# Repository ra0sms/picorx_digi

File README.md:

# SDR receiver Pico RX for DIGI modes

This is a clone of Jon Dawson's project [PicoRX SDR](https://github.com/dawsonjon/PicoRX).

But I wanted to make a simple DIGI (WSPR, FT8) receiver. This modification works with PC and WSJT-X software by one USB Type-C cable. 3.5 mm audio output is just for sound control. Audio from receiver to PC goes through USB connection.

More information - https://ra0sms.com/picorx-digi-modes

Firmware for 3 type of boards - https://github.com/ra0sms/picorx_digi/tree/main/firmware

Gerber files - https://github.com/ra0sms/picorx_digi/blob/main/KiCad/pico_rx/gerber_picorxdigi.zip

More pictures - https://github.com/ra0sms/picorx_digi/tree/main/pics

Schematic - https://github.com/ra0sms/picorx_digi/blob/main/KiCad/pico_rx/pipicorx.pdf

## Settings

You need to connect receiver to PC by USB cable. And select COM-port and Audio input like on the pictures below.

Or if you use FLrig software

Now you can see decodes.

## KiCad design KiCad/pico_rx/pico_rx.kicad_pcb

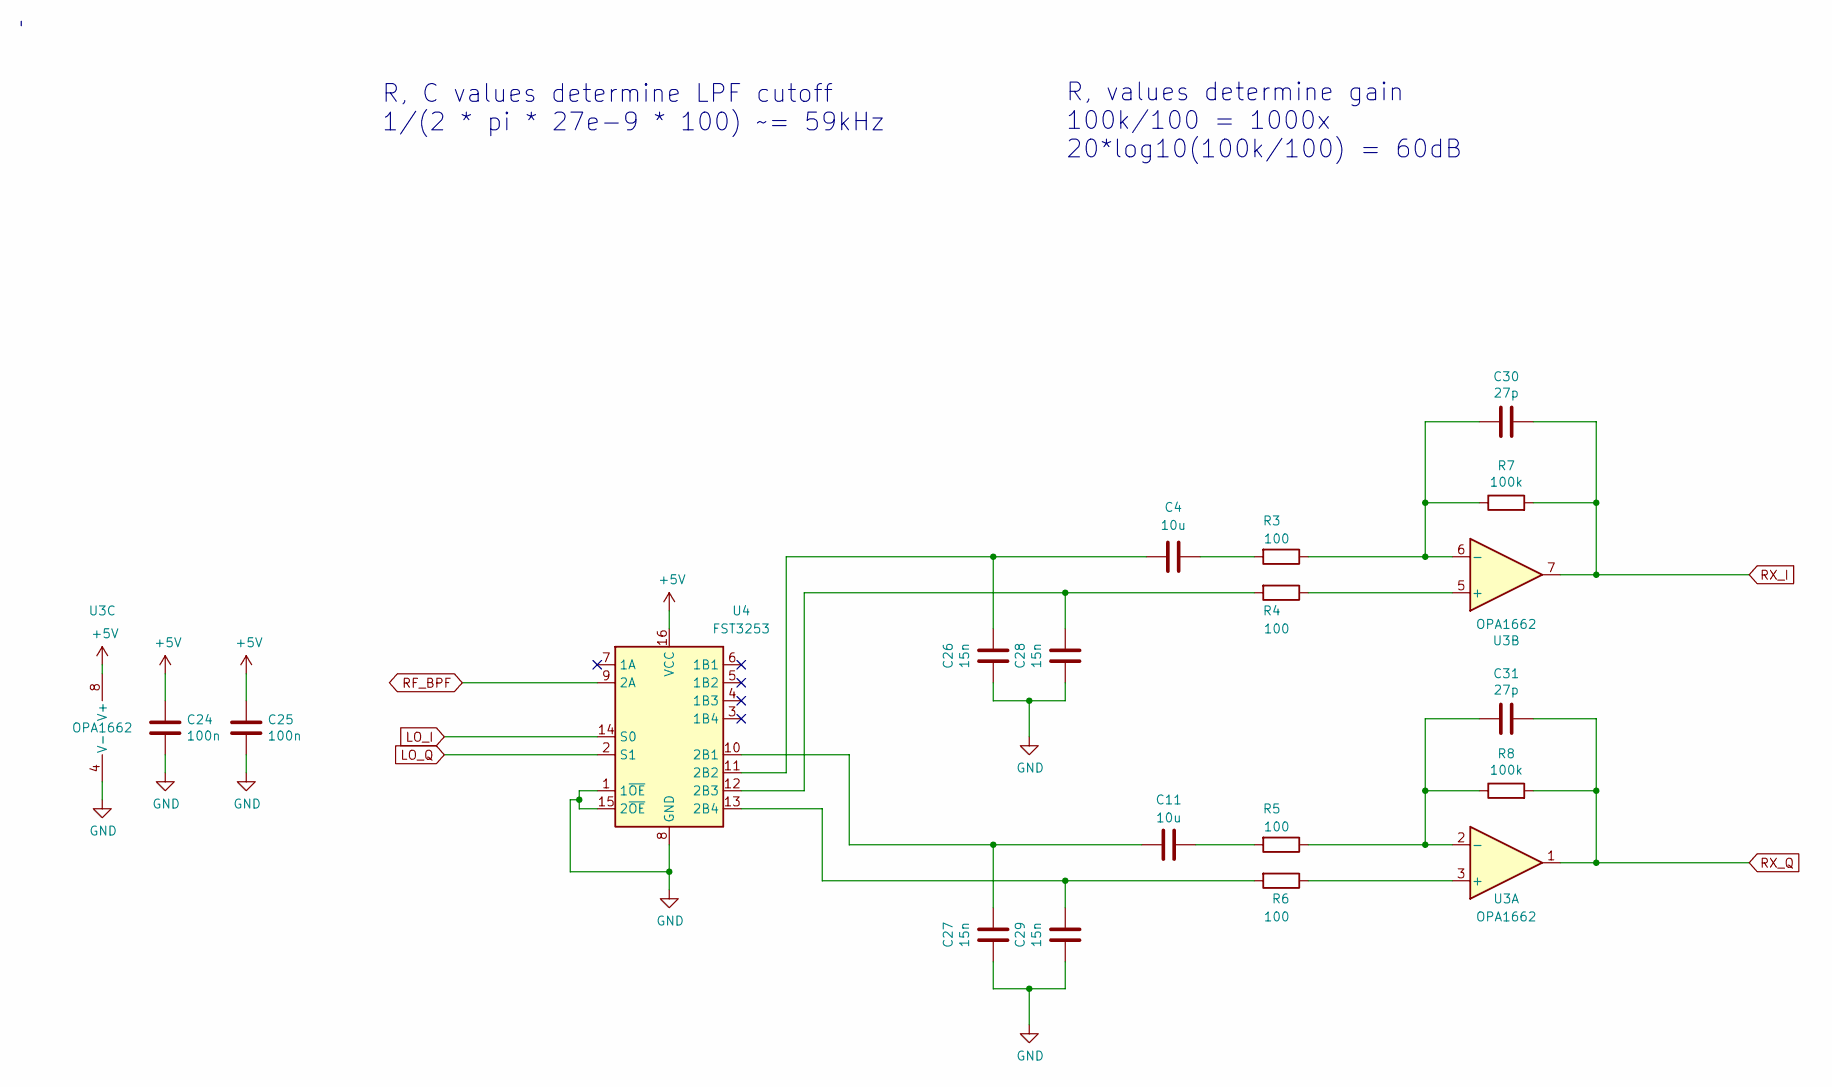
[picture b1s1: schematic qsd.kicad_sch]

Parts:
C4, C11: 10u; C_1206_3216Metric
C24, C25: 100n; C_1206_3216Metric
C26, C27, C28, C29: 15n; C_1206_3216Metric
C30, C31: 27p; C_1206_3216Metric
R3, R4, R5, R6: 100; R_1206_3216Metric
R7, R8: 100k; R_1206_3216Metric
U3: OPA1662; SO-8_3.9x4.9mm_P1.27mm
U4: FST3253; SOIC-16_3.9x9.9mm_P1.27mm

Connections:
+5V: C24.1, C25.1, U3.8 (V+), U4.16 (VCC); also elsewhere on the board
GND: C24.2, C25.2, C26.1, C27.1, C28.1, C29.1, U3.4 (V-), U4.1 (1~OE), U4.8 (GND), U4.15 (2~OE); also elsewhere on the board
LO_I: U4.14 (S0); also elsewhere on the board
LO_Q: U4.2 (S1); also elsewhere on the board
unnamed: C4.1, R3.2
unnamed: C11.1, R5.2
unnamed: R6.1, U3.3 (+)
unnamed: C31.1, R5.1, R8.1, U3.2 (-)
unnamed: R4.1, U3.5 (+)
unnamed: C30.1, R3.1, R7.1, U3.6 (-)
unnamed: C11.2, C27.2, U4.10 (2B1)
unnamed: C4.2, C26.2, U4.11 (2B2)
unnamed: C28.2, R4.2, U4.12 (2B3)
unnamed: C29.2, R6.2, U4.13 (2B4)
RF_BPF: U4.9 (2A); also elsewhere on the board
RX_I: C30.2, R7.2, U3.7; also elsewhere on the board
RX_Q: C31.2, R8.2, U3.1; also elsewhere on the board

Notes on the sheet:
R, values determine gain 100k/100 = 1000x 20*log10(100k/100) = 60dB
R, C values determine LPF cutoff 1/(2 * pi * 27e-9 * 100) ~= 59kHz

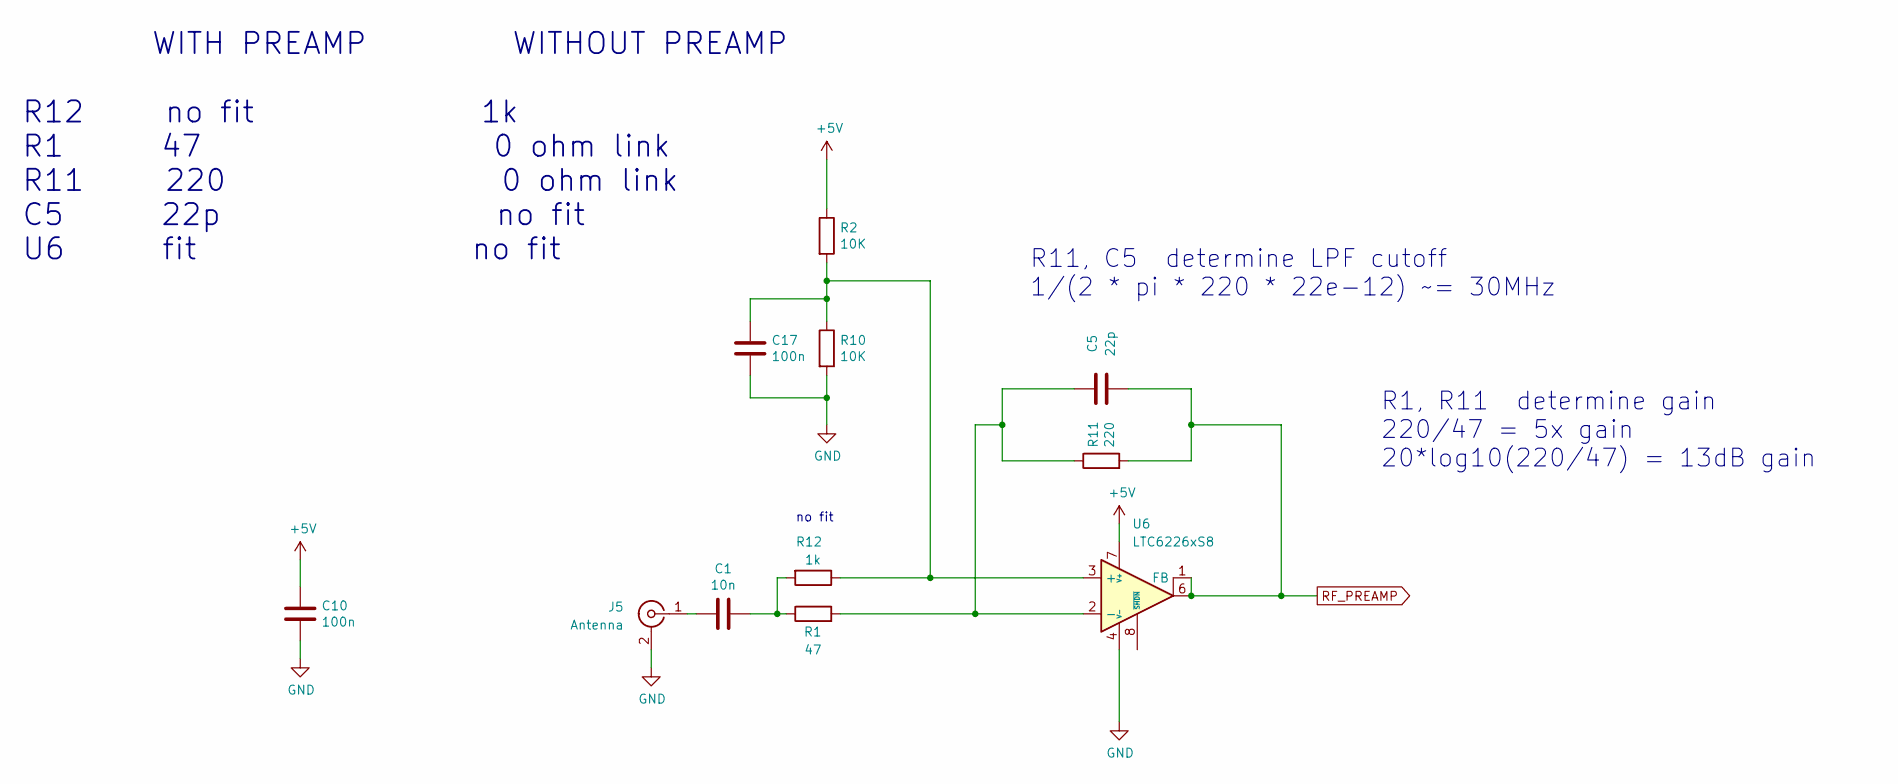
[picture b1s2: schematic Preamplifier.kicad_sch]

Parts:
C1: 10n; C_1206_3216Metric
C5: 22p; C_1206_3216Metric
C10, C17: 100n; C_1206_3216Metric
J5: Antenna; SMA_BAT_Wireless_BWSMA-KWE-Z001
R1: 47; R_1206_3216Metric
R2, R10: 10K; R_1206_3216Metric
R11: 220; R_1206_3216Metric
R12: 1k; R_1206_3216Metric
U6: LTC6226xS8; SO-8_3.9x4.9mm_P1.27mm

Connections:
+5V: C10.1, R2.1, U6.7 (V+); also elsewhere on the board
GND: C10.2, C17.2, J5.2 (Ext), R10.2, U6.4 (V-), U6.5 (V-); also elsewhere on the board
unnamed: C1.1, R1.1, R12.2
unnamed: C1.2, J5.1 (In)
unnamed: C17.1, R2.2, R10.1, R12.1, U6.3 (+)
unnamed: C5.1, R1.2, R11.1, U6.2 (-)
RF_PREAMP: C5.2, R11.2, U6.1 (FB), U6.6; also elsewhere on the board

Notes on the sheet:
no fit
R11, C5 determine LPF cutoff 1/(2 * pi * 220 * 22e-12) ~= 30MHz
WITH PREAMP WITHOUT PREAMP R12 no fit 1k R1 47 0 ohm link R11 220 0 ohm link C5 22p no fit U6 fit no fit
R1, R11 determine gain 220/47 = 5x gain 20*log10(220/47) = 13dB gain

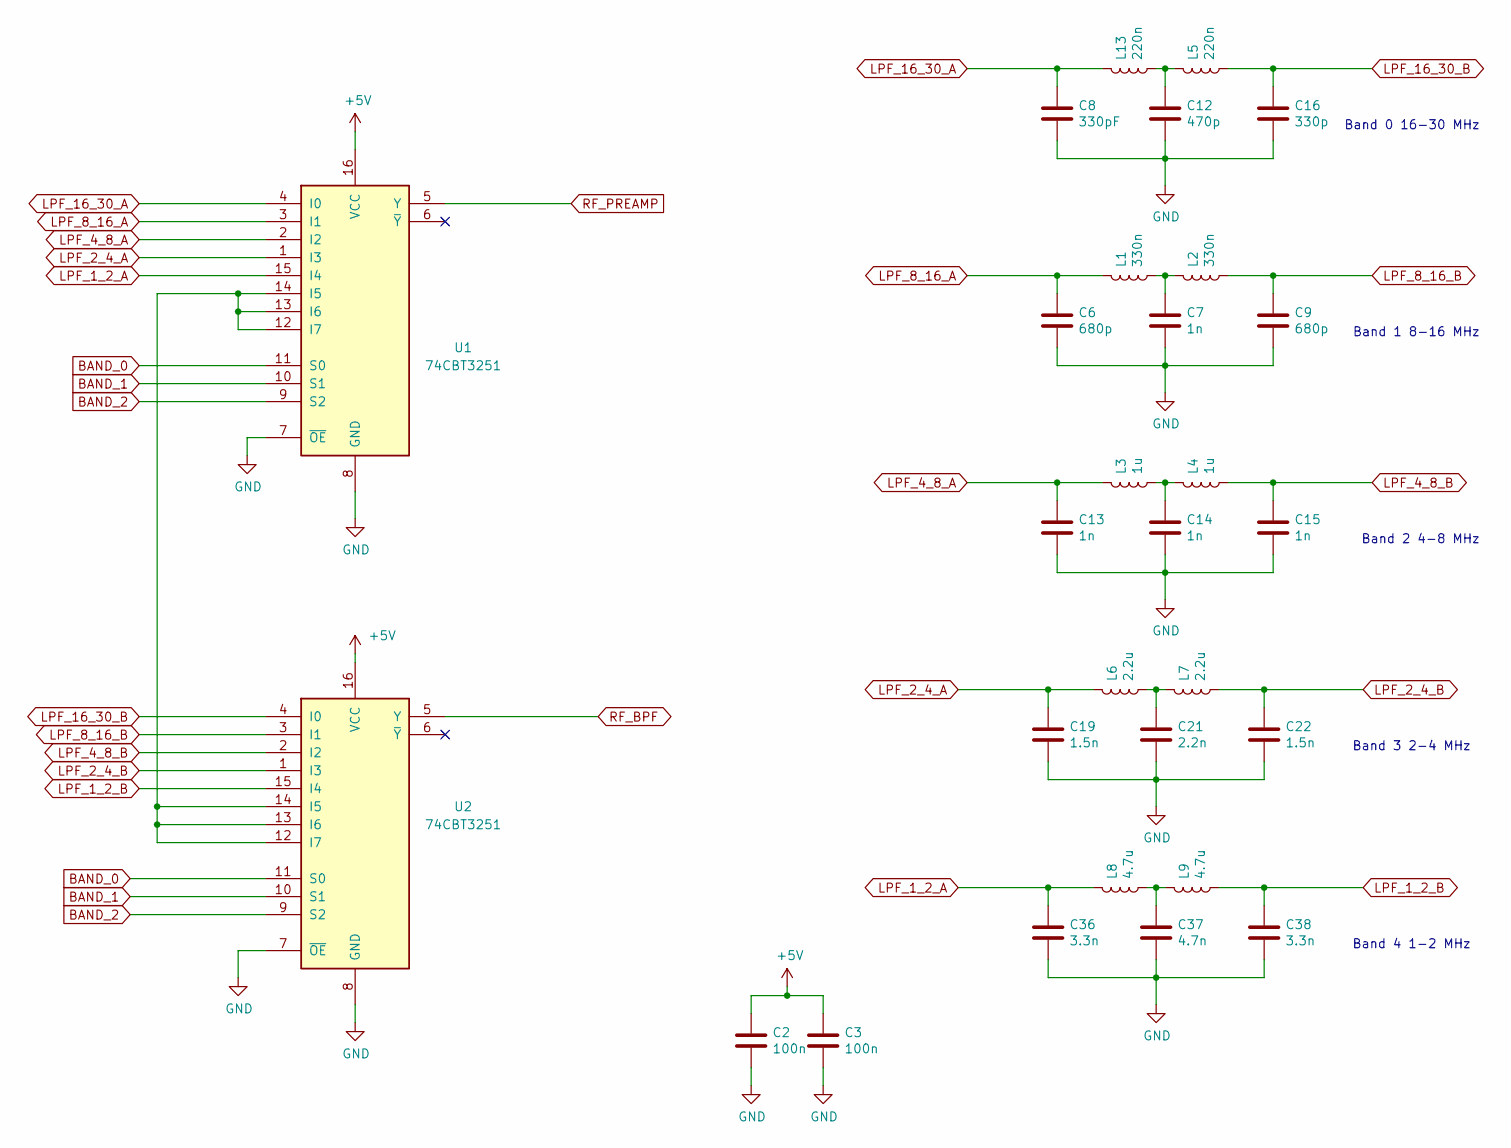
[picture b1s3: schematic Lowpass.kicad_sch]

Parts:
C2, C3: 100n; C_1206_3216Metric
C6, C9: 680p; C_0805_2012Metric
C7, C13, C14, C15: 1n; C_0805_2012Metric
C8: 330pF; C_0805_2012Metric
C12: 470p; C_0805_2012Metric
C16: 330p; C_0805_2012Metric
C19, C22: 1.5n; C_0805_2012Metric
C21: 2.2n; C_0805_2012Metric
C36, C38: 3.3n; C_0805_2012Metric
C37: 4.7n; C_0805_2012Metric
L1, L2: 330n; L_0805_2012Metric_Pad1.05x1.20mm_HandSolder
L3, L4: 1u; L_0805_2012Metric_Pad1.05x1.20mm_HandSolder
L5, L13: 220n; L_0805_2012Metric_Pad1.05x1.20mm_HandSolder
L6, L7: 2.2u; L_0805_2012Metric_Pad1.05x1.20mm_HandSolder
L8, L9: 4.7u; L_0805_2012Metric_Pad1.05x1.20mm_HandSolder
U1, U2: 74CBT3251; SSOP-16_5.3x6.2mm_P0.65mm

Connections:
+5V: C2.1, C3.1, U1.16 (VCC), U2.16 (VCC); also elsewhere on the board
BAND_0: U1.11 (S0), U2.11 (S0); also elsewhere on the board
BAND_1: U1.10 (S1), U2.10 (S1); also elsewhere on the board
BAND_2: U1.9 (S2), U2.9 (S2); also elsewhere on the board
GND: C2.2, C3.2, C6.1, C7.1, C8.1, C9.1, C12.1, C13.1, C14.1, C15.1, C16.1, C19.1, C21.1, C22.1, C36.1, C37.1, C38.1, U1.7 (~OE), U1.8 (GND), U2.7 (~OE), U2.8 (GND); also elsewhere on the board
LPF_1_2_A: C36.2, L8.2, U1.15 (I4)
LPF_1_2_B: C38.2, L9.1, U2.15 (I4)
LPF_2_4_A: C19.2, L6.2, U1.1 (I3)
LPF_2_4_B: C22.2, L7.1, U2.1 (I3)
LPF_4_8_A: C13.2, L3.2, U1.2 (I2)
LPF_4_8_B: C15.2, L4.1, U2.2 (I2)
LPF_8_16_A: C6.2, L1.2, U1.3 (I1)
LPF_8_16_B: C9.2, L2.1, U2.3 (I1)
LPF_16_30_A: C8.2, L13.2, U1.4 (I0)
LPF_16_30_B: C16.2, L5.1, U2.4 (I0)
unnamed: C7.2, L1.1, L2.2
unnamed: C12.2, L5.2, L13.1
unnamed: C14.2, L3.1, L4.2
unnamed: C21.2, L6.1, L7.2
unnamed: C37.2, L8.1, L9.2
unnamed: U1.12 (I7), U1.13 (I6), U1.14 (I5), U2.12 (I7), U2.13 (I6), U2.14 (I5)
RF_BPF: U2.5 (Y); also elsewhere on the board
RF_PREAMP: U1.5 (Y); also elsewhere on the board

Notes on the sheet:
Band 2 4-8 MHz
Band 4 1-2 MHz
Band 1 8-16 MHz
Band 3 2-4 MHz
Band 0 16-30 MHz

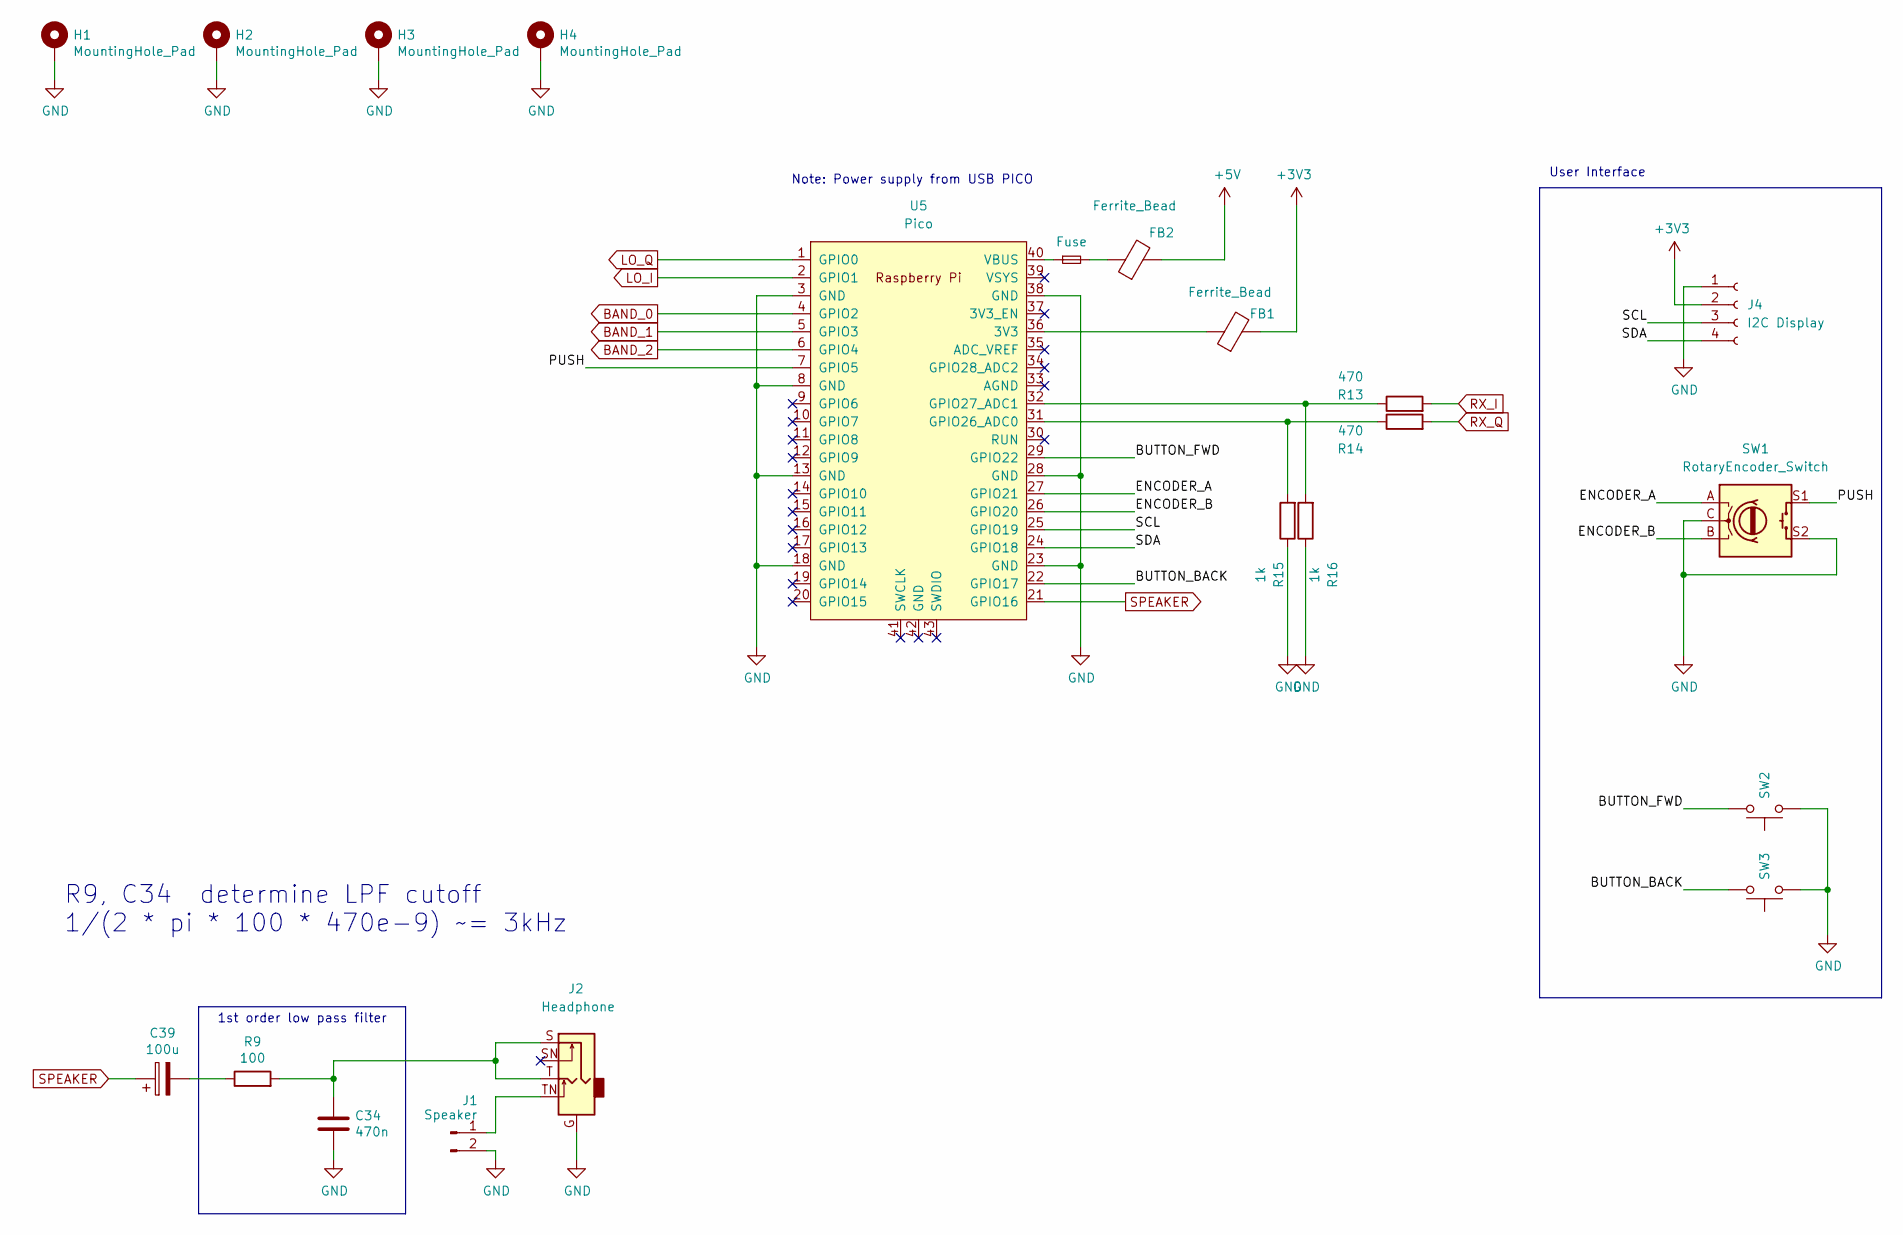
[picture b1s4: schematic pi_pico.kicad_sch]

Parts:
C34: 470n; C_0805_2012Metric
C39: 100u; CP_Radial_D5.0mm_P2.50mm
F1: Fuse; L_1206_3216Metric
FB1, FB2: Ferrite_Bead; L_1206_3216Metric
H1, H2, H3, H4: MountingHole_Pad; MountingHole_3.2mm_M3_Pad
J1: Speaker; PinHeader_1x02_P2.54mm_Vertical
J2: Headphone; jack3.5mm switched
J4: I2C Display; SDD1306
R9: 100; R_0805_2012Metric
R13, R14: 470; R_1206_3216Metric
R15, R16: 1k; R_1206_3216Metric
SW1: RotaryEncoder_Switch; RotaryEncoder_Alps_EC11E-Switch_Vertical_H20mm
SW2, SW3: SW_Push; SW_Tactile_SPST_Angled_PTS645Vx31-2LFS
U5: Pico; RPi_Pico_SMD_TH

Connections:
+3V3: FB1.2, J4.2
+5V: FB2.2; also elsewhere on the board
/PI Pico/BUTTON_BACK: SW3.2, U5.22 (GPIO17)
/PI Pico/BUTTON_FWD: SW2.2, U5.29 (GPIO22)
/PI Pico/ENCODER_A: SW1.A, U5.27 (GPIO21)
/PI Pico/ENCODER_B: SW1.B, U5.26 (GPIO20)
/PI Pico/PUSH: SW1.S1, U5.7 (GPIO5)
/PI Pico/SCL: J4.3, U5.25 (GPIO19)
/PI Pico/SDA: J4.4, U5.24 (GPIO18)
BAND_0: U5.4 (GPIO2); also elsewhere on the board
BAND_1: U5.5 (GPIO3); also elsewhere on the board
BAND_2: U5.6 (GPIO4); also elsewhere on the board
GND: C34.2, H1.1, H2.1, H3.1, H4.1, J1.2, J2.G, J4.1, R15.1, R16.1, SW1.C, SW1.S2, SW2.1, SW3.1, U5.3 (GND), U5.8 (GND), U5.13 (GND), U5.18 (GND), U5.23 (GND), U5.28 (GND), U5.38 (GND); also elsewhere on the board
LO_I: U5.2 (GPIO1); also elsewhere on the board
LO_Q: U5.1 (GPIO0); also elsewhere on the board
unnamed: C34.1, J2.S, J2.T, R9.2
unnamed: C39.2, R9.1
unnamed: F1.2, FB2.1
unnamed: J1.1, J2.TN
unnamed: FB1.1, U5.36 (3V3)
unnamed: R14.1, R15.2, U5.31 (GPIO26_ADC0)
unnamed: R13.1, R16.2, U5.32 (GPIO27_ADC1)
unnamed: F1.1, U5.40 (VBUS)
RX_I: R13.2; also elsewhere on the board
RX_Q: R14.2; also elsewhere on the board
SPEAKER: C39.1, U5.21 (GPIO16)

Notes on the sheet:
1st order low pass filter
Note: Power supply from USB PICO
User Interface
R9, C34 determine LPF cutoff 1/(2 * pi * 100 * 470e-9) ~= 3kHz

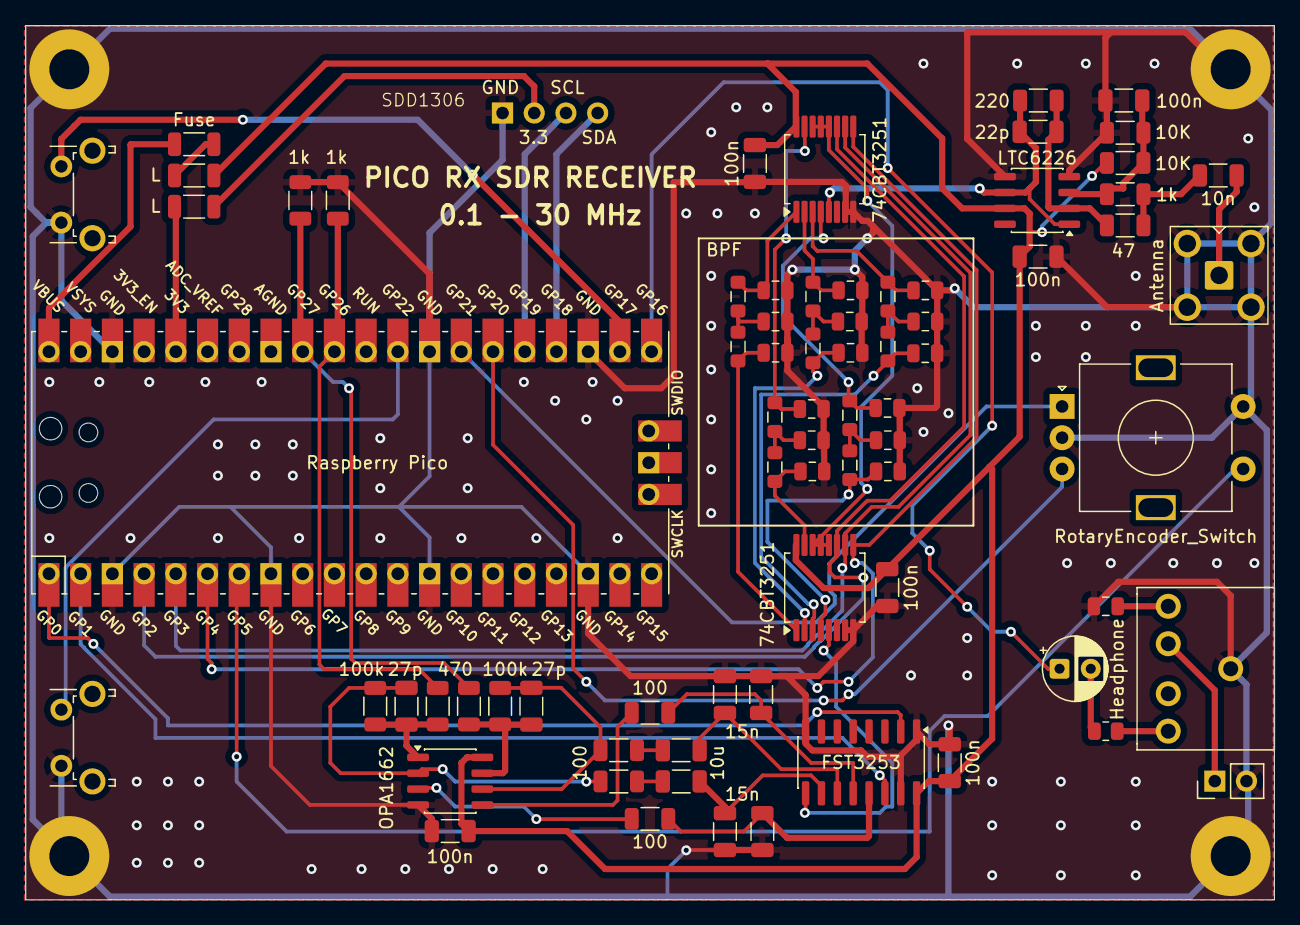
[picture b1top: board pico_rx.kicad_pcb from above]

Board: 2 copper layers, 100.0 x 70.0 mm, 79 parts (0 on the bottom side), 58 nets.

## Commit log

2026-01-21 add readme
